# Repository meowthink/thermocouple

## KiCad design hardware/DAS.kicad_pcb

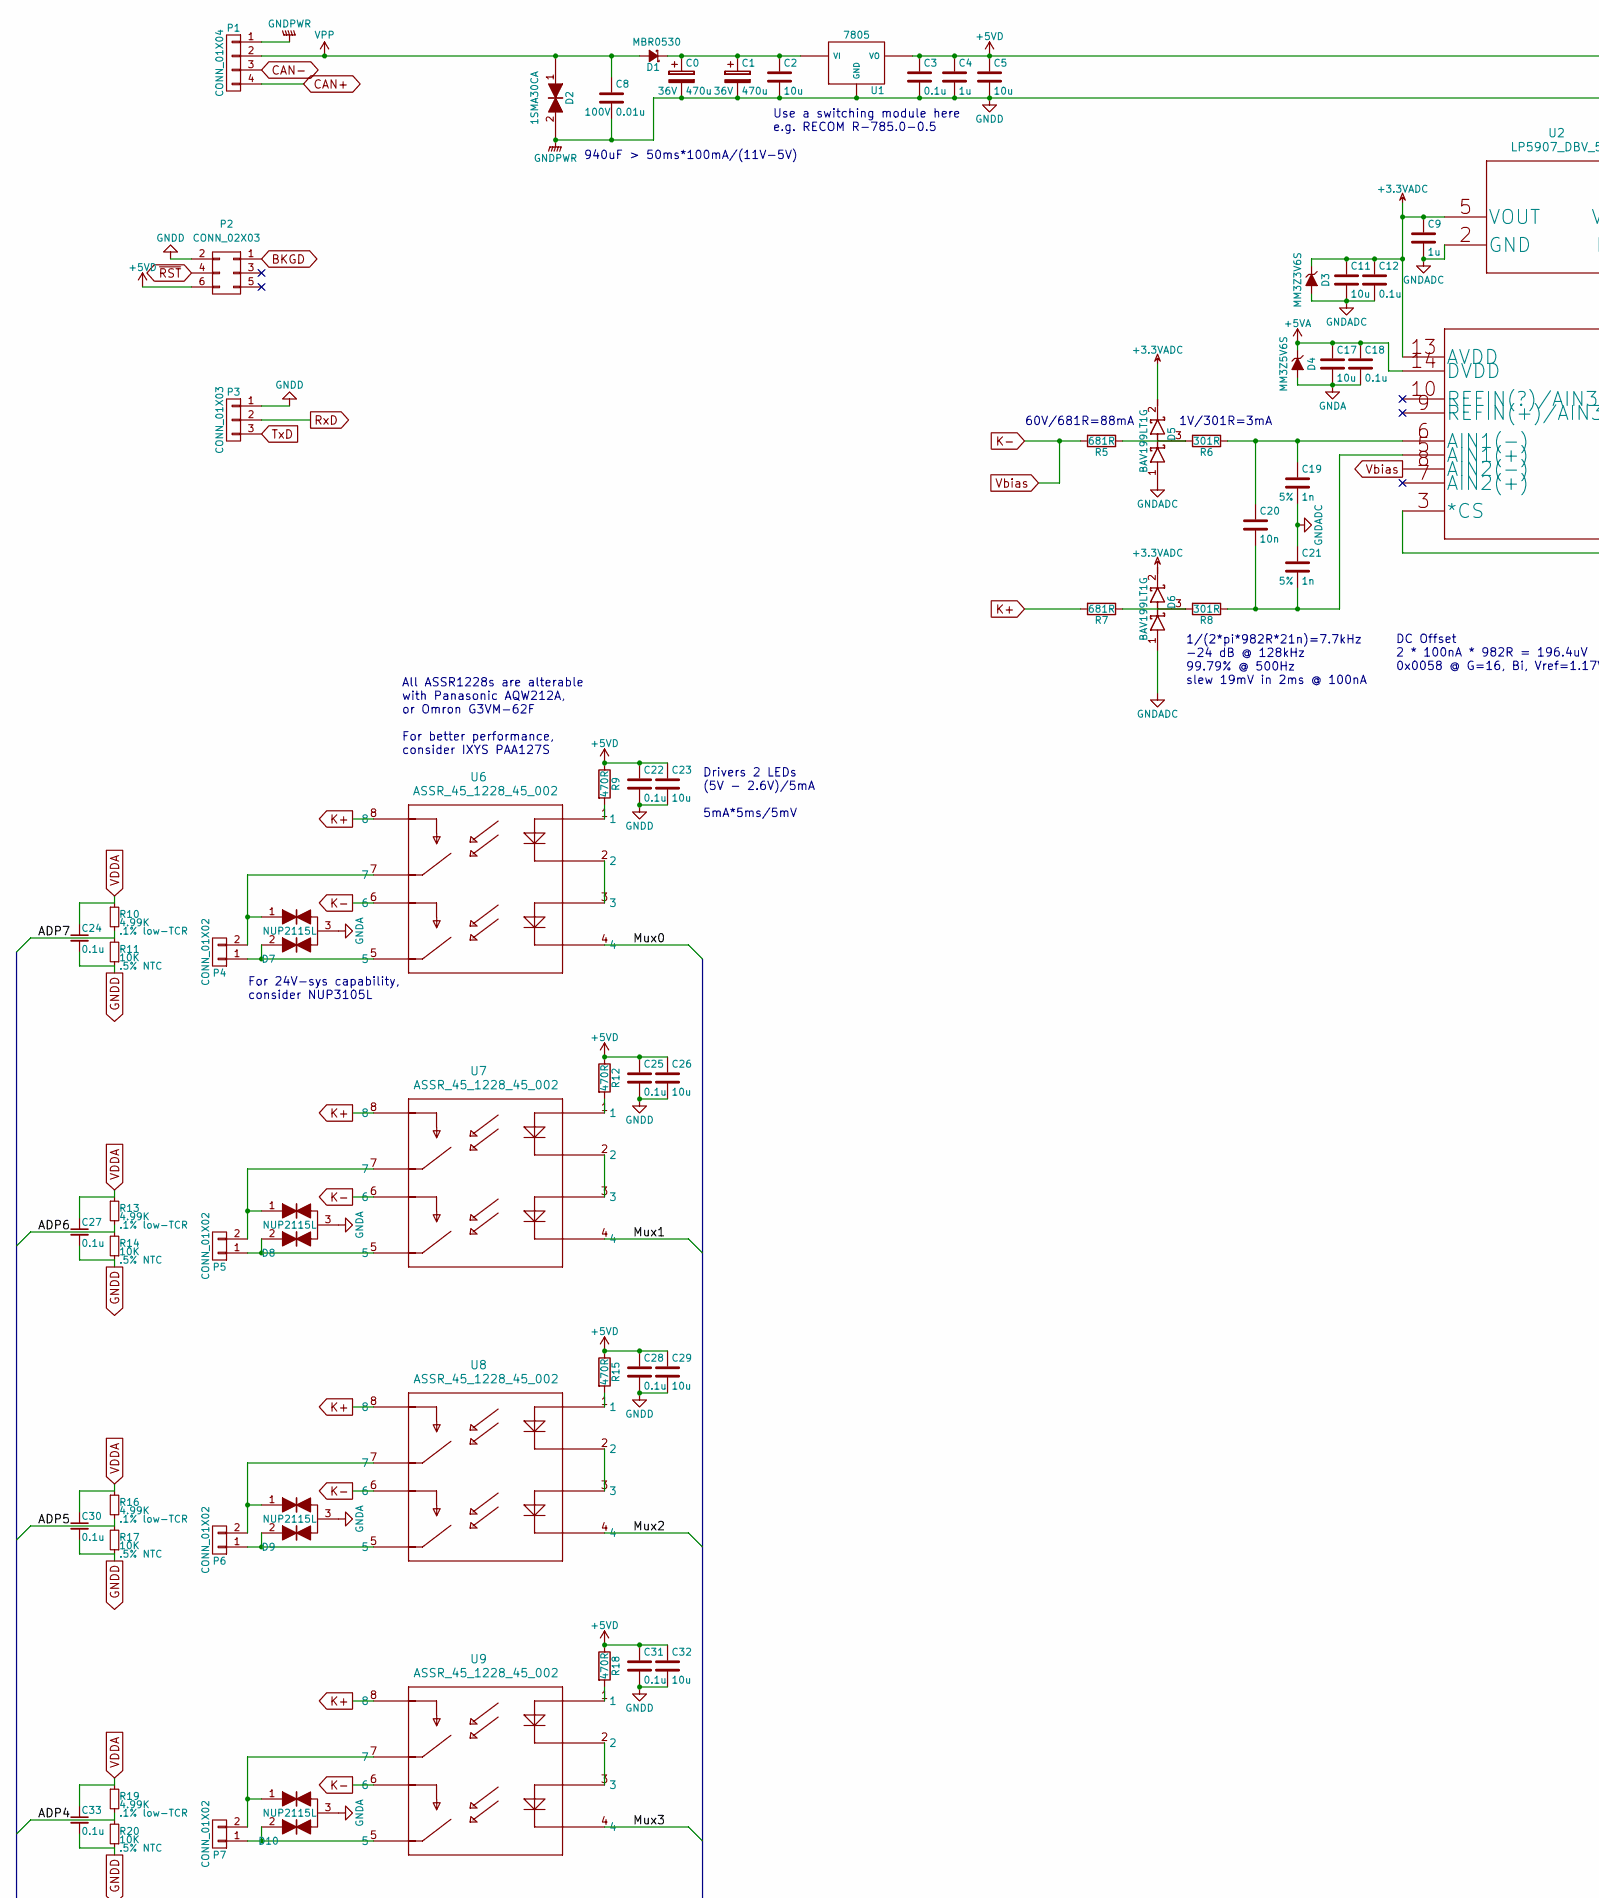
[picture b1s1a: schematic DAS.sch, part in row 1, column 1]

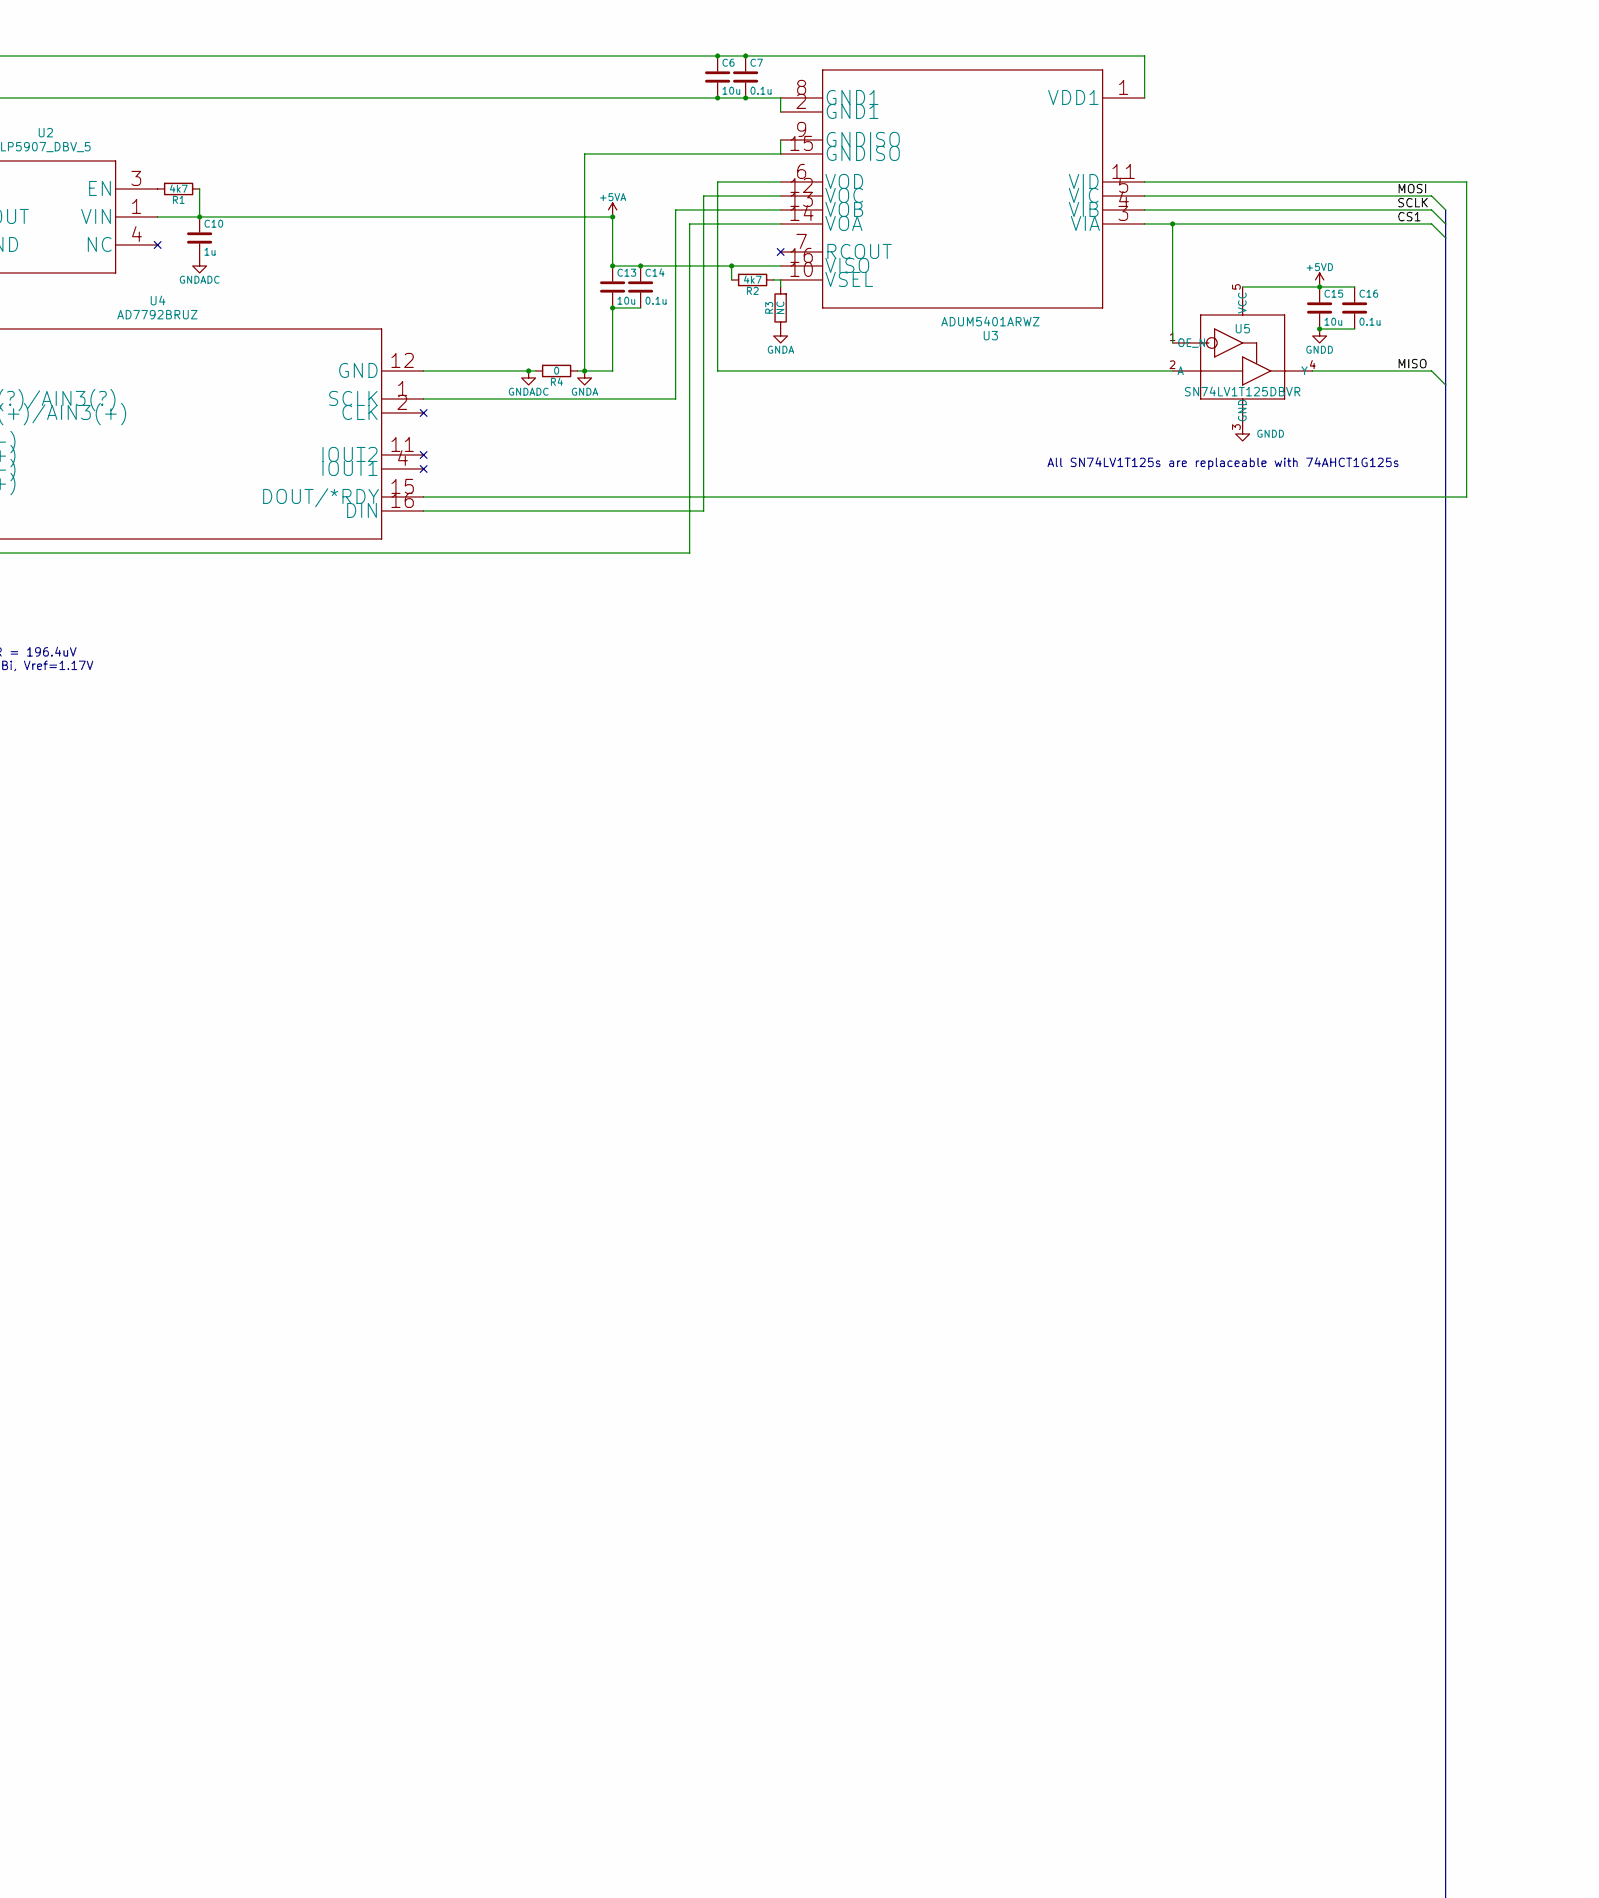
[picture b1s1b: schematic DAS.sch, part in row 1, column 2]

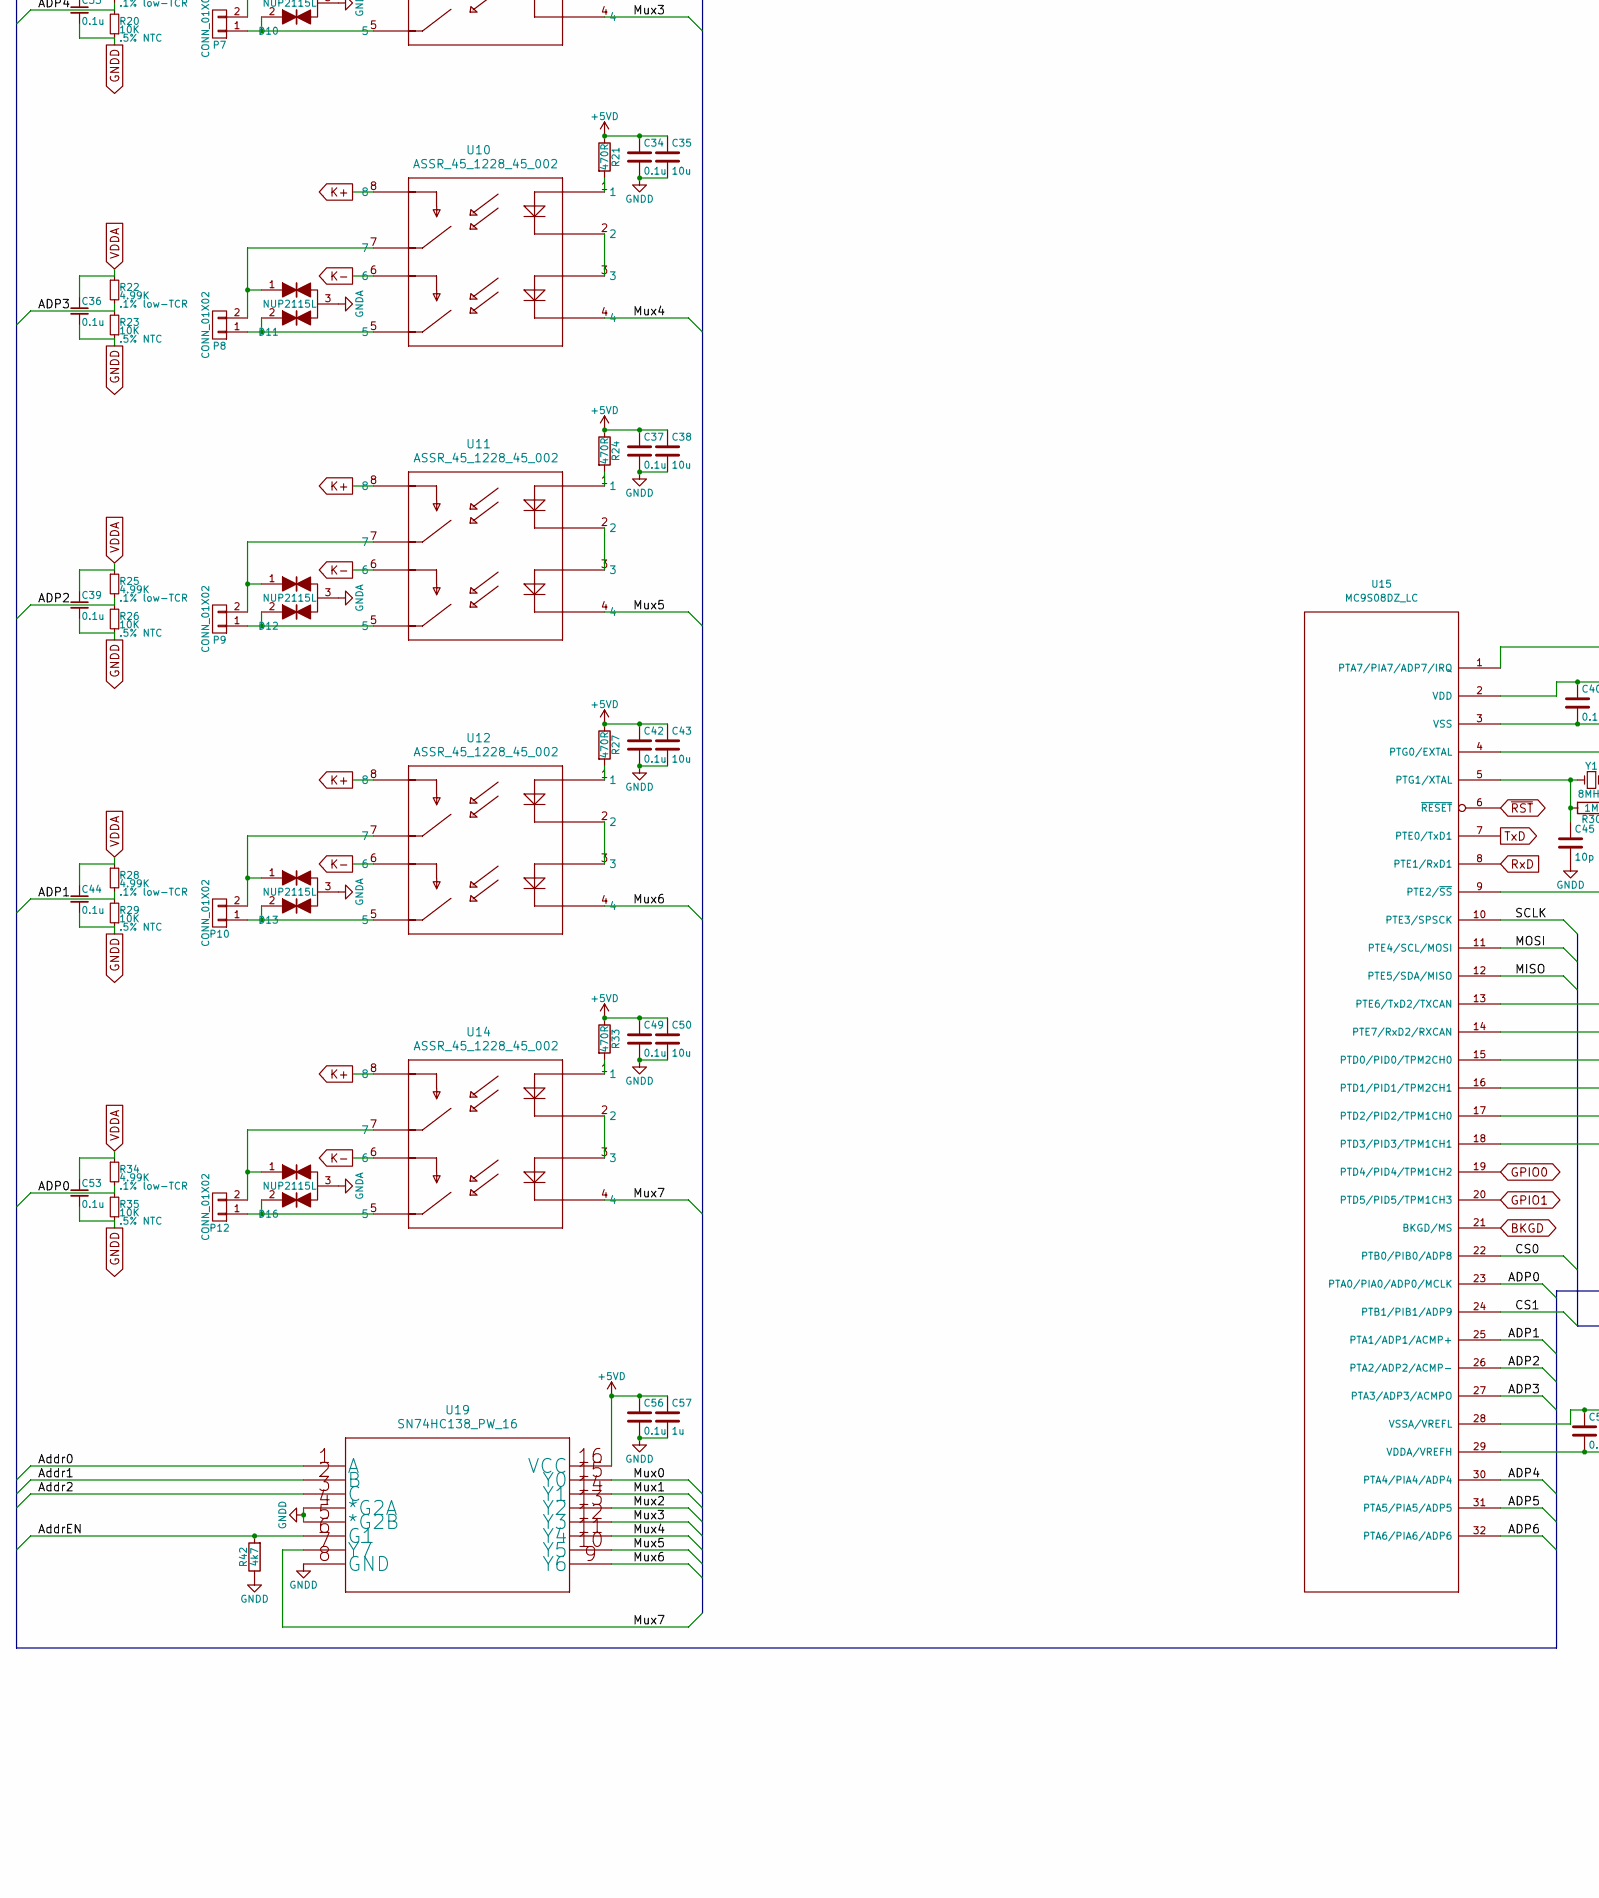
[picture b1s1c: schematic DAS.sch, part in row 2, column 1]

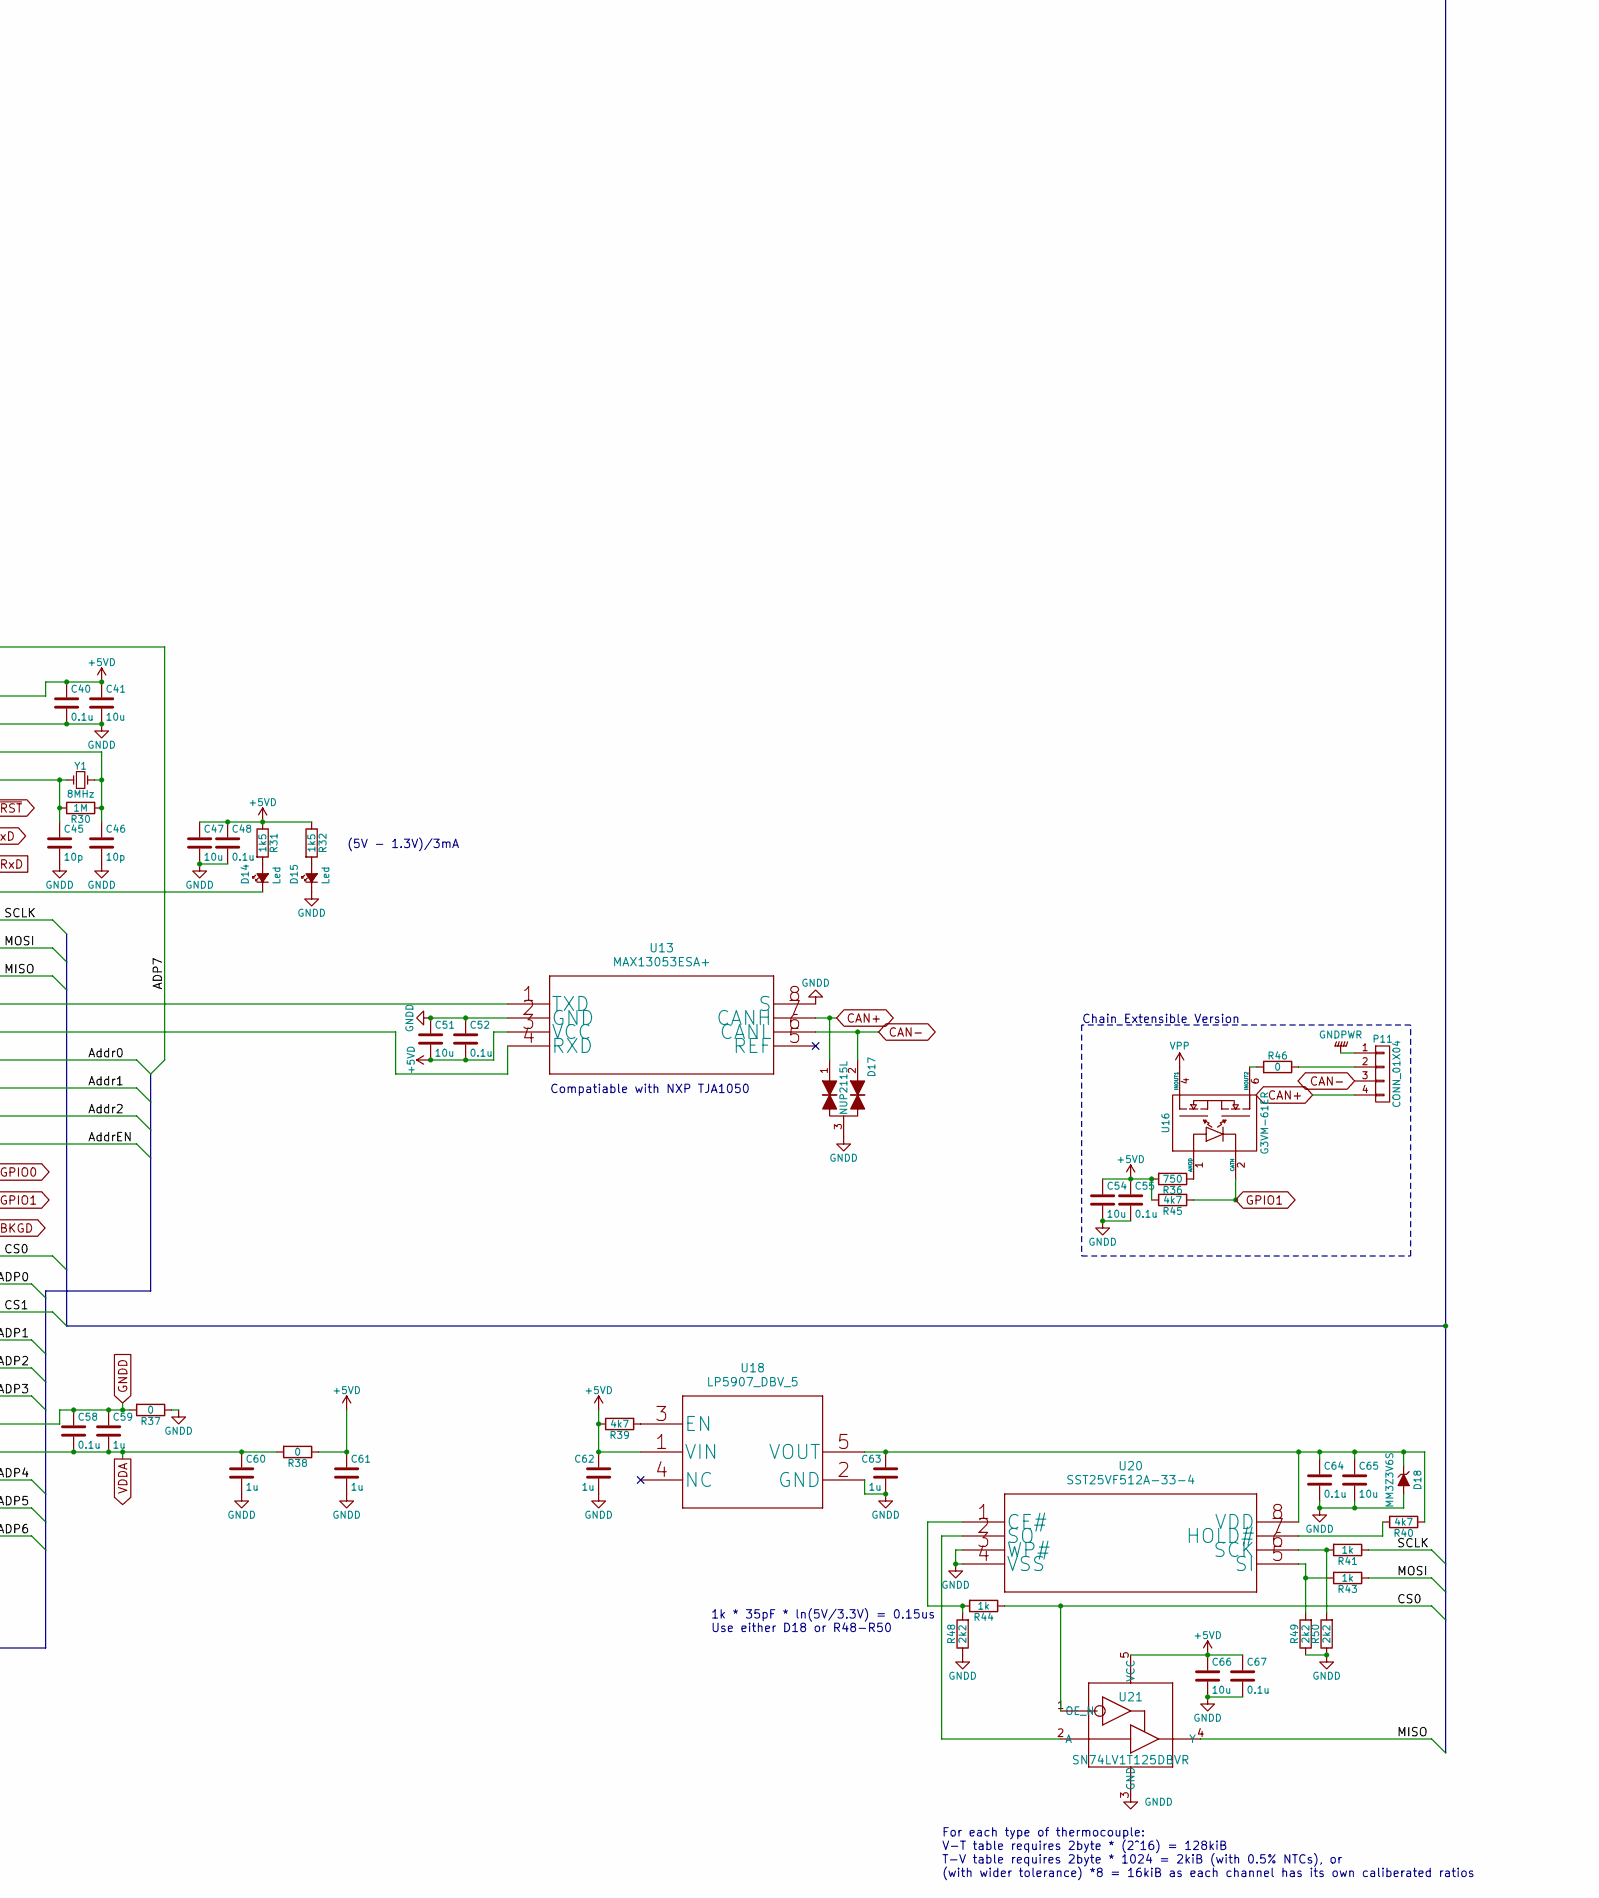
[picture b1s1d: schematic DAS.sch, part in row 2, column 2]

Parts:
C0, C1: 470u; c_elec_10x10.5
C2, C5, C6, C11, C13, C15, C17, C23, C26, C29, C32, C35, C38, C41, C43, C47, C50, C51, C54, C65, C66: 10u; C_0805
C3, C7, C12, C14, C16, C18, C22, C24, C25, C27, C28, C30, C31, C33, C34, C36, C37, C39, C40, C42, C44, C48, C49, C52, C53, C55, C56, C58, C64, C67: 0.1u; C_0805
C4, C9, C10, C57, C59, C60, C61, C62, C63: 1u; C_0805
C8: 0.01u; C_0805
C19, C21: 1n; C_0805
C20: 10n; C_0805
C45, C46: 10p; C_0805
D1: MBR0530; SOD-123
D2: 1SMA30CA; SMA_Standard
D3, D18: MM3Z3V6S; SOD-323
D4: MM3Z5V6S; SOD-323
D5, D6: BAV199LT1G; SOT-23
D7, D8, D9, D10, D11, D12, D13, D16, D17: NUP2115L; SOT-23
D14, D15: Led; LED-5MM
P1, P11: CONN_01X04; Pin_Header_Straight_1x04
P2: CONN_02X03; Pin_Header_Straight_2x03
P3: CONN_01X03; Pin_Header_Straight_1x03
P4, P5, P6, P7, P8, P9, P10, P12: CONN_01X02; Thermocouple
R1, R2, R39, R40, R42, R45: 4k7; R_0805
R3: NC; R_0805
R4, R37, R38, R46: 0; R_0805
R5, R7: 681R; R_0805
R6, R8: 301R; R_0805
R9, R12, R15, R18, R21, R24, R27, R33: 470R; R_0805
R10, R13, R16, R19, R22, R25, R28, R34: 4.99K; R_0805
R11, R14, R17, R20, R23, R26, R29, R35: 10K; Thermoresistor
R30: 1M; R_0805
R31, R32: 1k5; R_0805
R36: 750; R_0805
R41, R43, R44: 1k; R_0805
R48, R49, R50: 2k2; R_0805
U1: 7805; DCDC-Conv_Recom_R-78HBxx-0.5
U2, U18: LP5907_DBV_5
U3: ADUM5401ARWZ; ADUM5401WCRWZ
U4: AD7792BRUZ
U5, U21: SN74LV1T125DBVR
U6, U7, U8, U9, U10, U11, U12, U14: ASSR_45_1228_45_002; SMD-8
U13: MAX13053ESA+
U15: MC9S08DZ_LC; LQFP-32_7x7mm_Pitch0.8mm
U16: G3VM-61ER; SMD-6
U19: SN74HC138_PW_16
U20: SST25VF512A-33-4
Y1: 8MHz; Crystal_HC49-SD_SMD

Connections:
+3.3VADC: C9.1, C11.1, C12.1, D3.1 (K), D5.2 (K), D6.2 (K), U2.5 (VOUT), U4.13 (AVDD)
+5VA: C10.1, C13.1, C14.1, C17.1, C18.1, D4.1 (K), R1.1, R2.2, U2.1 (VIN), U3.16 (VISO), U4.14 (DVDD)
+5VD: C3.1, C4.1, C5.1, C6.1, C7.1, C15.1, C16.1, C22.1, C23.1, C25.1, C26.1, C28.1, C29.1, C31.1, C32.1, C34.1, C35.1, C37.1, C38.1, C40.1, C41.1, C42.1, C43.1, C47.1, C48.1, C49.1, C50.1, C51.2, C52.2, C54.1, C55.1, C56.1, C57.1, C61.1, C62.1, C66.1, C67.1, P2.6, R9.1, R12.1, R15.1, R18.1, R21.1, R24.1, R27.1, R31.1, R32.1, R33.1, R36.2, R38.1, R39.1, R45.1, U1.1 (VO), U3.1 (VDD1), U5.5 (VCC), U13.3 (VCC), U15.2 (VDD), U18.1 (VIN), U19.16 (VCC), U21.5 (VCC)
/ADP0: R34.2, R35.2, U15.23 (PTA0/PIA0/ADP0/MCLK)
/ADP1: R28.2, R29.2, U15.25 (PTA1/ADP1/ACMP+)
/ADP2: R25.2, R26.2, U15.26 (PTA2/ADP2/ACMP-)
/ADP3: R22.2, R23.2, U15.27 (PTA3/ADP3/ACMPO)
/ADP4: R19.2, R20.2, U15.30 (PTA4/PIA4/ADP4)
/ADP5: R16.2, R17.2, U15.31 (PTA5/PIA5/ADP5)
/ADP6: R13.2, R14.2, U15.32 (PTA6/PIA6/ADP6)
/ADP7: R10.2, R11.2, U15.1 (PTA7/PIA7/ADP7/IRQ)
/Addr0: U15.15 (PTD0/PID0/TPM2CH0), U19.1 (A)
/Addr1: U15.16 (PTD1/PID1/TPM2CH1), U19.2 (B)
/Addr2: U15.17 (PTD2/PID2/TPM1CH0), U19.3 (C)
/AddrEN: R42.2, U15.18 (PTD3/PID3/TPM1CH1), U19.6 (G1)
/CS0: R44.1, U15.22 (PTB0/PIB0/ADP8), U21.1 (OE_N)
/CS1: U3.3 (VIA), U5.1 (OE_N), U15.24 (PTB1/PIB1/ADP9)
/MISO: U5.4 (Y), U15.12 (PTE5/SDA/MISO), U21.4 (Y)
/MOSI: R43.1, U3.5 (VIC), U15.11 (PTE4/SCL/MOSI)
/Mux0: U6.4, U19.15 (Y0)
/Mux1: U7.4, U19.14 (Y1)
/Mux2: U8.4, U19.13 (Y2)
/Mux3: U9.4, U19.12 (Y3)
/Mux4: U10.4, U19.11 (Y4)
/Mux5: U11.4, U19.10 (Y5)
/Mux6: U12.4, U19.9 (Y6)
/Mux7: U14.4, U19.7 (Y7)
/SCLK: R41.1, U3.4 (VIB), U15.10 (PTE3/SPSCK)
BKGD: P2.1, U15.21 (BKGD/MS)
CAN+: D17.1, P1.4, P11.4, U13.7 (CANH)
CAN-: D17.2, P1.3, P11.3, U13.6 (CANL)
GNDA: C13.2, C14.2, C17.2, C18.2, D4.2 (A), D7.3, D8.3, D9.3, D10.3, D11.3, D12.3, D13.3, D16.3, R3.1, R4.1, U3.9 (GNDISO), U3.15 (GNDISO)
GNDADC: C9.2, C10.2, C11.2, C12.2, C19.2, C21.1, D3.2 (A), D5.1 (A), D6.1 (A), R4.2, U2.2 (GND), U4.12 (GND)
GNDD: C0.2, C1.2, C2.2, C3.2, C4.2, C5.2, C6.2, C7.2, C8.2, C15.2, C16.2, C22.2, C23.2, C24.2, C25.2, C26.2, C27.2, C28.2, C29.2, C30.2, C31.2, C32.2, C33.2, C34.2, C35.2, C36.2, C37.2, C38.2, C39.2, C40.2, C41.2, C42.2, C43.2, C44.2, C45.2, C46.2, C47.2, C48.2, C49.2, C50.2, C51.1, C52.1, C53.2, C54.2, C55.2, C56.2, C57.2, C58.1, C59.1, C60.2, C61.2, C62.2, C63.2, C64.2, C65.2, C66.2, C67.2, D2.2, D15.1 (K), D17.3, D18.2 (A), P1.1, P2.2, P3.1, P11.1, R11.1, R14.1, R17.1, R20.1, R23.1, R26.1, R29.1, R35.1, R37.1, R37.2, R42.1, R48.1, R49.1, R50.1, U1.2 (GND), U3.2 (GND1), U3.8 (GND1), U5.3 (GND), U13.2 (GND), U13.8 (S), U15.3 (VSS), U15.28 (VSSA/VREFL), U18.2 (GND), U19.4 (*G2A), U19.5 (*G2B), U19.8 (GND), U20.3 (WP#), U20.4 (VSS), U21.3 (GND)
GPIO0: U15.19 (PTD4/PID4/TPM1CH2)
GPIO1: R45.2, U15.20 (PTD5/PID5/TPM1CH3), U16.2 (CATH)
K+: R7.2, U6.8, U7.8, U8.8, U9.8, U10.8, U11.8, U12.8, U14.8
K-: R5.2, U4.8 (AIN2(-)), U6.6, U7.6, U8.6, U9.6, U10.6, U11.6, U12.6, U14.6
unnamed: C0.1, C1.1, C2.1, D1.1 (K), U1.3 (VI)
unnamed: C19.1, C20.1, R6.1, U4.6 (AIN1(-))
unnamed: C20.2, C21.2, R8.1, U4.5 (AIN1(+))
unnamed: C45.1, R30.1, U15.5 (PTG1/XTAL), Y1.1
unnamed: C46.1, R30.2, U15.4 (PTG0/EXTAL), Y1.2
unnamed: C63.1, C64.1, C65.1, D18.1 (K), R40.1, U18.5 (VOUT), U20.8 (VDD)
unnamed: D5.3 (common), R5.1, R6.2
unnamed: D6.3 (common), R7.1, R8.2
unnamed: D7.1, P4.2, U6.7
unnamed: D7.2, P4.1, U6.5
unnamed: D8.1, P5.2, U7.7
unnamed: D8.2, P5.1, U7.5
unnamed: D9.1, P6.2, U8.7
unnamed: D9.2, P6.1, U8.5
unnamed: D10.1, P7.2, U9.7
unnamed: D10.2, P7.1, U9.5
unnamed: D11.1, P8.2, U10.7
unnamed: D11.2, P8.1, U10.5
unnamed: D12.1, P9.2, U11.7
unnamed: D12.2, P9.1, U11.5
unnamed: D13.1, P10.2, U12.7
unnamed: D13.2, P10.1, U12.5
unnamed: D14.1 (K), U15.9 (PTE2/~SS)
unnamed: D14.2 (A), R31.2
unnamed: D15.2 (A), R32.2
unnamed: D16.1, P12.2, U14.7
unnamed: D16.2, P12.1, U14.5
unnamed: P11.2, R46.1
unnamed: R1.2, U2.3 (EN)
unnamed: R2.1, R3.2, U3.10 (VSEL)
unnamed: R9.2, U6.1
unnamed: R12.2, U7.1
unnamed: R15.2, U8.1
unnamed: R18.2, U9.1
unnamed: R21.2, U10.1
unnamed: R24.2, U11.1
unnamed: R27.2, U12.1
unnamed: R33.2, U14.1
unnamed: R36.1, U16.1 (ANOD)
unnamed: R39.2, U18.3 (EN)
unnamed: R40.2, U20.7 (HOLD#)
unnamed: R41.2, R50.2, U20.6 (SCK)
unnamed: R43.2, R49.2, U20.5 (SI)
unnamed: R44.2, R48.2, U20.1 (CE#)
unnamed: R46.2, U16.6 (INOUT2)
unnamed: U3.6 (VOD), U5.2 (A)
unnamed: U3.11 (VID), U4.15 (DOUT/*RDY)
unnamed: U3.12 (VOC), U4.16 (DIN)
unnamed: U3.13 (VOB), U4.1 (SCLK)
unnamed: U3.14 (VOA), U4.3 (*CS)
unnamed: U6.2, U6.3
unnamed: U7.2, U7.3
unnamed: U8.2, U8.3
unnamed: U9.2, U9.3
unnamed: U10.2, U10.3
unnamed: U11.2, U11.3
unnamed: U12.2, U12.3
unnamed: U13.1 (TXD), U15.13 (PTE6/TxD2/TXCAN)
unnamed: U13.4 (RXD), U15.14 (PTE7/RxD2/RXCAN)
unnamed: U14.2, U14.3
unnamed: U20.2 (SO), U21.2 (A)
RxD: P3.2, U15.8 (PTE1/RxD1)
TxD: P3.3, U15.7 (PTE0/TxD1)
VDDA: C24.1, C27.1, C30.1, C33.1, C36.1, C39.1, C44.1, C53.1, C58.2, C59.2, C60.1, R10.1, R13.1, R16.1, R19.1, R22.1, R25.1, R28.1, R34.1, R38.2, U15.29 (VDDA/VREFH)
VPP: C8.1, D1.2 (A), D2.1, P1.2, U16.4 (INOUT1)
~RST: P2.4, U15.6 (~RESET)

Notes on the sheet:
Use a switching module here e.g. RECOM R-785.0-0.5
Drivers 2 LEDs (5V - 2.6V)/5mA 5mA*5ms/5mV
1V/301R=3mA
60V/681R=88mA
1/(2*pi*982R*21n)=7.7kHz -24 dB @ 128kHz 99.79% @ 500Hz slew 19mV in 2ms @ 100nA
All ASSR1228s are alterable with Panasonic AQW212A, or Omron G3VM-62F For better performance, consider IXYS PAA127S
DC Offset 2 * 100nA * 982R = 196.4uV 0x0058 @ G=16, Bi, Vref=1.17V
For 24V-sys capability, consider NUP3105L
All SN74LV1T125s are replaceable with 74AHCT1G125s
940uF > 50ms*100mA/(11V-5V)
Compatiable with NXP TJA1050
(5V - 1.3V)/3mA
Chain Extensible Version
For each type of thermocouple: V-T table requires 2byte * (2^16) = 128kiB T-V table requires 2byte * 1024 = 2kiB (with 0.5% NTCs), or (with wider tolerance) *8 = 16kiB as each channel has its own caliberated ratios
1k * 35pF * ln(5V/3.3V) = 0.15us Use either D18 or R48-R50

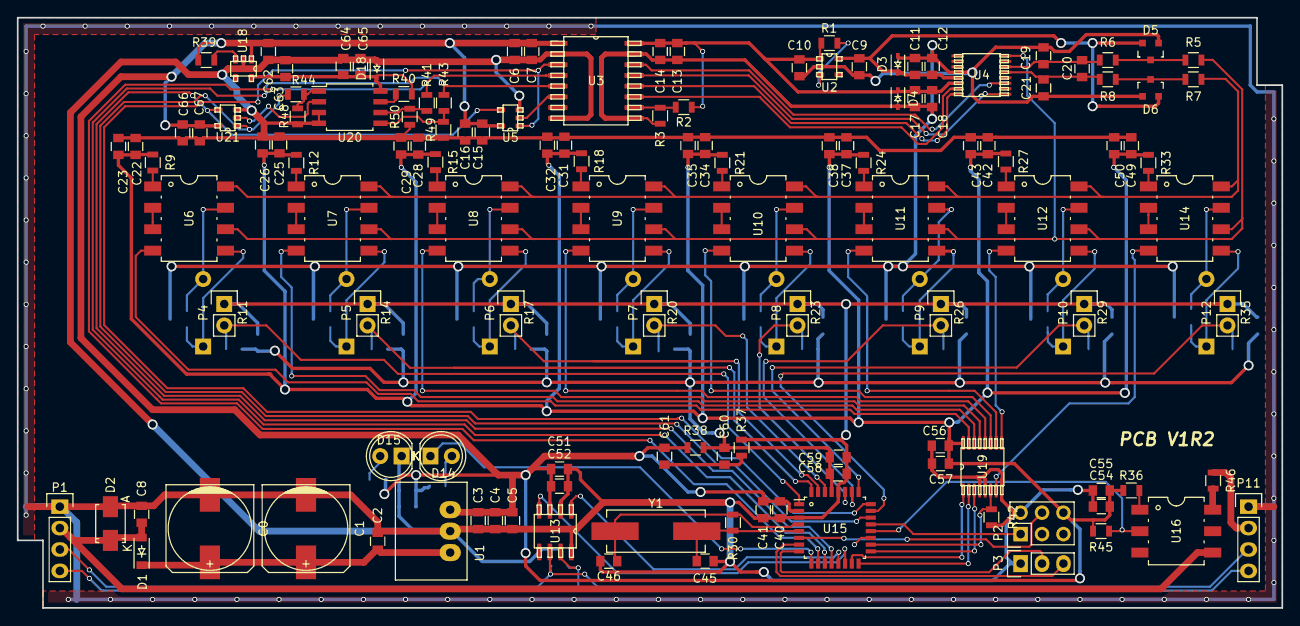
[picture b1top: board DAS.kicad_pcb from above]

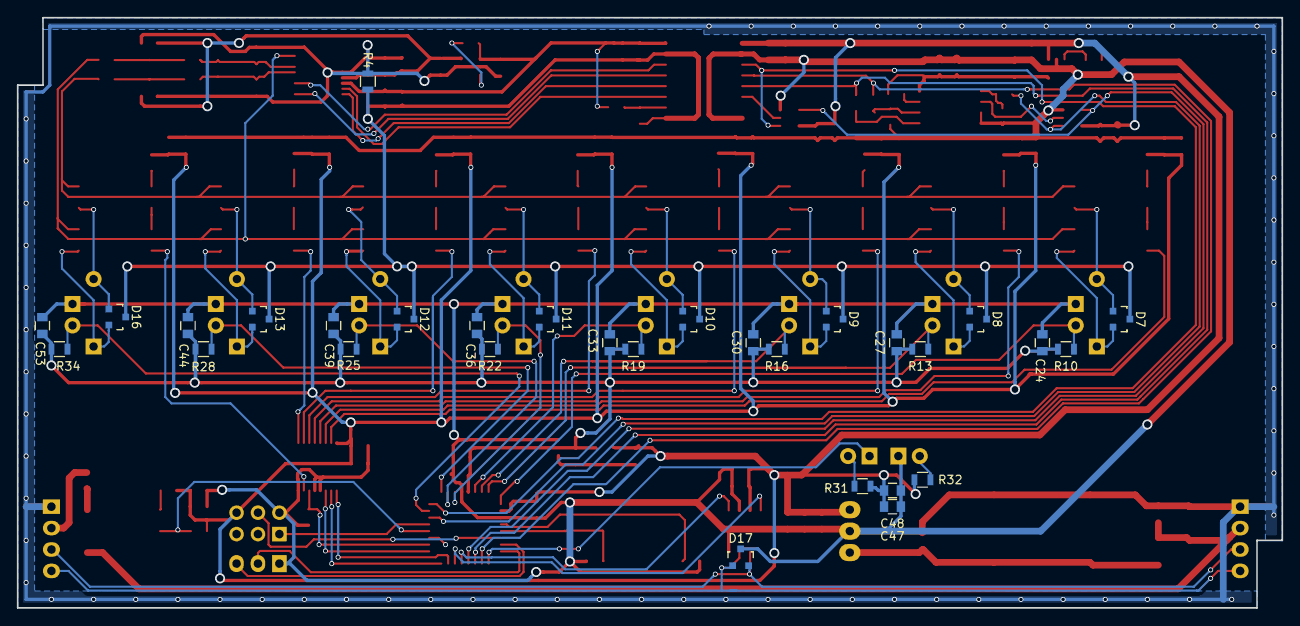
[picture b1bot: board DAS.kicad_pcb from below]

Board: 2 copper layers, 150.0 x 70.0 mm, 168 parts (30 on the bottom side), 103 nets.

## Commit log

2016-05-20 Initial commit. A prototype has been made and tested to be functional.
2016-05-21 Try fix issues found out during prototyping. Misused LDO supplying VDDA removed. Wrong pin assignment to DC-DC module corrected. Footprint of SPI Flash tweaked to allow wider selection of parts. A pu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
2016-05-23 Prototype Firmware: Try to achieve higher precision on Cold-Junction compensation
2016-06-04 Prototype Firmware: Try fix misusing of CAN tx slots
